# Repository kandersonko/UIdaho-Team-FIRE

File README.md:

# Team FIRE GitHub
## University of Idaho
### Collin Heist, Shelby Linafelter, and Koffi Anderson

## Existing Files

-  `/Component Test Board/`
	* This directory is for the _KiCad_ project dedicated to the __Component Test Board__.

- `/Board Redesign/`
	* This directory is for the _KiCad_ project dedicated to the __IRIDIUM 9523 carrier redesign__.
	* Within this is __Iridium Carrier (2). *__ files. These files are the Eagle project files, and the previous Senior Design Team's (Team SCUBEE) schematic and PCB files being used for reference.
	* The redesigned project is being placed within `/KiCad Project/`, and this directory contains the Eeschema and PCBnew footprints and symbols created for the purpose of this board.
	
## To Do

- Find a replacement for the LT3959 Boost circuit
- Verify the final status of `JP4` (Sim Card Enable); whether it is tied to the 5V line or the SIM enable line coming from the IRIDIUM 9523
- Verify the status of `JP1` (mode switch pin of IRIDIUM) if it's tied to GND or to the status of `JP2`.
- Verify the status of `JP2` (mode switch high-voltage jumper); if it is tied to 3.3V ISENSE line or 3.3V bus.
- Verify the status of `JP3` (RF enable reference voltage); if it is tied to 3.3V ISENSE line or 3.3V bus.
- Determine whether `S1` (the RF enable switch?) is necessary in end-product.
- Verify the status of `JP5` (the VCCA power source of `U3`); is it tied to 3.3V ISENSE or 3.3V bus.
- Determine if `JP3` (the +3.3V, +5V, and bus power voltage 3-pin header) is required in end-product.
- Decided whether the SAMD21 is adequate, or should we transition over to the SAMD51 for memory / I2C capabilities.
- Determine whether `S2` (the microcontroller reset switch) is necessary in the final product.
- Identify which test points are essential / desired.

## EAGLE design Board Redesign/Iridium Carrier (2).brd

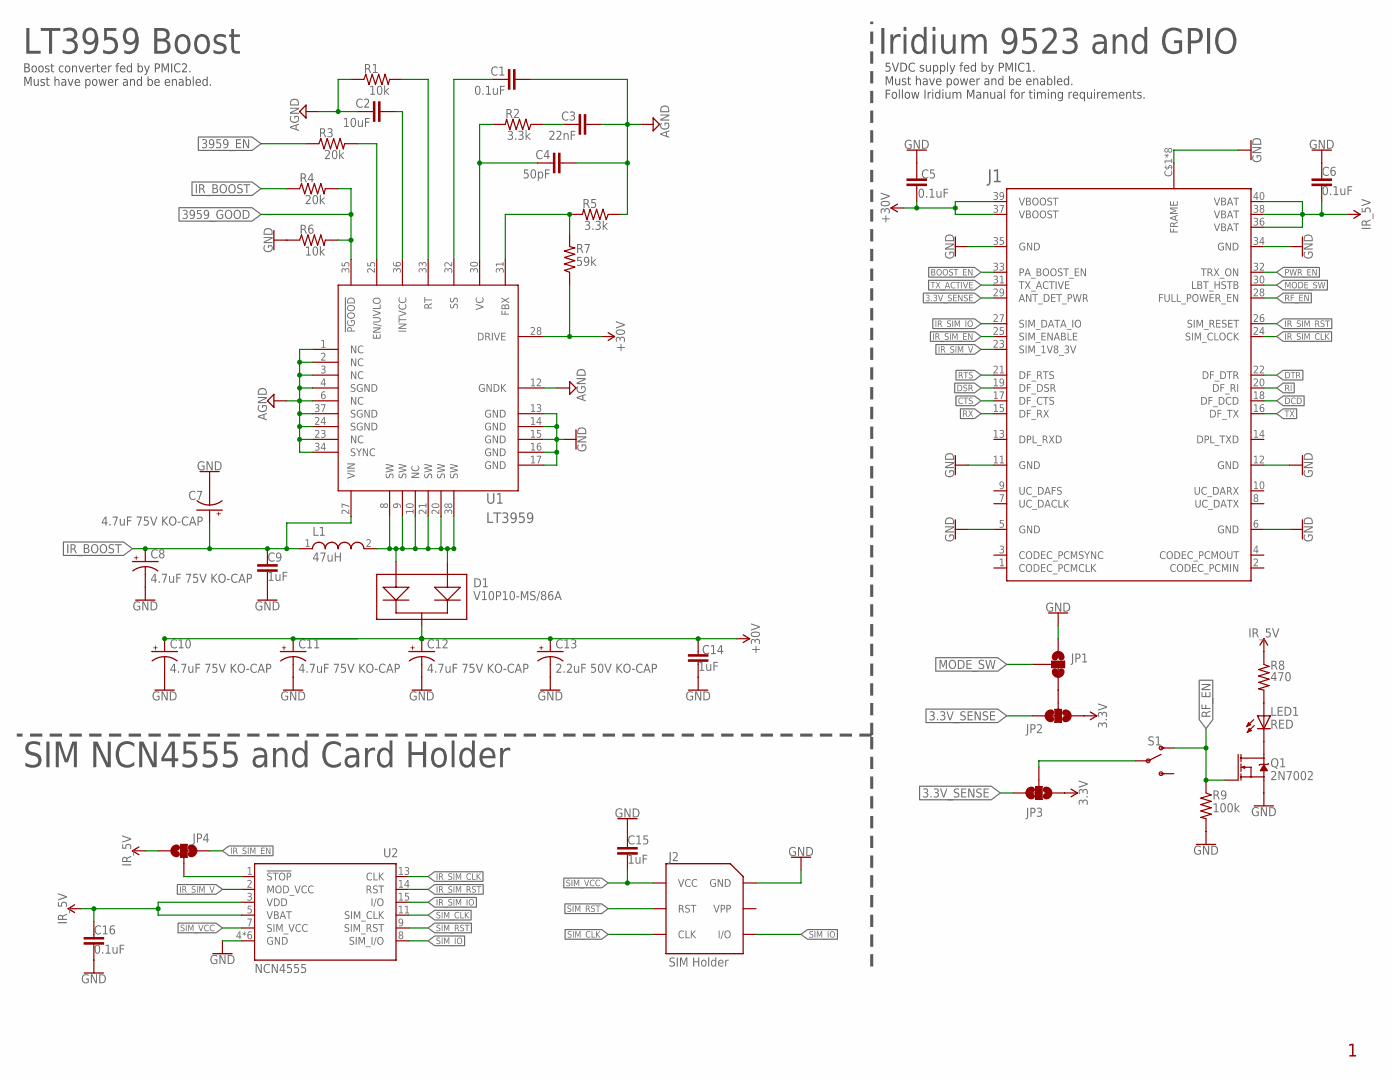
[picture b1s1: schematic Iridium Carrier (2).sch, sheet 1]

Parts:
C1, C5, C6, C16: 0.1uF; C0603
C2: 10uF; C0603
C3: 22nF; C0603
C4: 50pF; C0603
C7, C8, C10, C11, C12: 4.7uF 75V KO-CAP; D/7343-31R
C9, C14, C15: 1uF; C0603
C13: 2.2uF 50V KO-CAP; CT3528
D1: V10P10-MS/86A; DIODE_TO-277A
J1: Molex 0541020404; IRIDIUM-9523
J2: SIM Holder; SIMHOLDER
JP1: OP MODE; SMT-JUMPER_3_1-NC_TRACE_SILK
JP2, JP3: Sense V; SMT-JUMPER_3_1-NC_TRACE_SILK
JP4: SIM_STOP; SMT-JUMPER_3_1-NC_TRACE_SILK
L1: 47uH; WE-HCI_1890
LED1: RED; CHIP-LED0805
Q1: 2N7002; SOT23-3
R1, R6: 10k; R0603
R2, R5: 3.3k; R0603
R3, R4: 20k; R0603
R7: 59k; R0603
R8: 470; R0603
R9: 100k; R0603
S1: FULL RF PWR; SWITCH_SPDT_PTH_11.6X4.0MM
U1: LT3959; QFN-36_UHEMA
U2: DAVID-HANDY_ON_NCN4555DEFAULT; DAVID-HANDY_QFN16-3X3MM

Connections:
3.3V: JP2.1, JP3.1; also elsewhere on the board
3.3V_SENSE: J1.29 (ANT_DET_PWR), JP2.3, JP3.3; also elsewhere on the board
3959_EN: R3.1; also elsewhere on the board
3959_GOOD: R4.2, R6.2, U1.35 (!PGOOD!); also elsewhere on the board
AGND: C1.2, C2.1, C3.2, C4.2, R1.1, R5.1, U1.1 (NC), U1.2 (NC), U1.3 (NC), U1.4 (SGND), U1.6 (NC), U1.12 (GNDK), U1.23 (NC), U1.24 (SGND), U1.34 (SYNC), U1.37 (SGND)
BOOST_EN: J1.33 (PA_BOOST_EN); also elsewhere on the board
CTS: J1.17 (DF_CTS); also elsewhere on the board
DCD: J1.18 (DF_DCD); also elsewhere on the board
DSR: J1.19 (DF_DSR); also elsewhere on the board
DTR: J1.22 (DF_DTR); also elsewhere on the board
GND: C5.1, C6.1, C7.-, C8.-, C9.2, C10.-, C11.-, C12.-, C13.-, C14.2, C15.1, C16.1, J1.5 (GND), J1.6 (GND), J1.11 (GND), J1.12 (GND), J1.34 (GND), J1.35 (GND), J1.C$1 (FRAME), J1.C$2 (FRAME), J1.C$3 (FRAME), J1.C$4 (FRAME), J1.C$5 (FRAME), J1.C$6 (FRAME), J1.C$7 (FRAME), J1.C$8 (FRAME), J2.C5 (GND), JP1.1, Q1.2 (S), R6.1, R9.2, U1.13 (GND), U1.14 (GND), U1.15 (GND), U1.16 (GND), U1.17 (GND), U2.4 (GND), U2.6 (GND), U2.10 (GND), U2.12 (GND), U2.16 (GND), U2.EXT (GND); also elsewhere on the board
IR_BOOST: C7.+, C8.+, C9.1, L1.1, R4.1, U1.27 (VIN); also elsewhere on the board
IR_SIM_CLK: J1.24 (SIM_CLOCK), U2.13 (CLK)
IR_SIM_EN: J1.25 (SIM_ENABLE), JP4.3; also elsewhere on the board
IR_SIM_IO: J1.27 (SIM_DATA_IO), U2.15 (I/O)
IR_SIM_RST: J1.26 (SIM_RESET), U2.14 (RST)
IR_SIM_V: J1.23 (SIM_1V8_3V), U2.2 (MOD_VCC)
MODE_SW: J1.30 (LBT_HSTB), JP1.2
unnamed: JP4.2, U2.1 (!STOP)
unnamed: D1.1, D1.2, L1.2, U1.8 (SW), U1.9 (SW), U1.10 (NC), U1.20 (SW), U1.21 (SW), U1.38 (SW)
unnamed: C2.2, U1.36 (INTVCC)
unnamed: JP1.3, JP2.2
unnamed: C1.1, U1.32 (SS)
unnamed: R1.2, U1.33 (RT)
unnamed: LED1.C, Q1.3 (D)
unnamed: C4.1, R2.2, U1.30 (VC)
unnamed: C3.1, R2.1
unnamed: R5.2, R7.2, U1.31 (FBX)
unnamed: JP3.2, S1.2
unnamed: LED1.A, R8.2
unnamed: R3.2, U1.25 (EN/UVLO)
PWR_EN: J1.32 (TRX_ON); also elsewhere on the board
RF_EN: J1.28 (FULL_POWER_EN), Q1.1 (G), R9.1, S1.1 (O); also elsewhere on the board
RI: J1.20 (DF_RI); also elsewhere on the board
RTS: J1.21 (DF_RTS); also elsewhere on the board
RX: J1.15 (DF_RX); also elsewhere on the board
SIM_CLK: J2.C3 (CLK), U2.11 (SIM_CLK)
SIM_IO: J2.C7 (I/O), U2.8 (SIM_I/O)
SIM_RST: J2.C2 (RST), U2.9 (SIM_RST)
SIM_VCC: C15.2, J2.C1 (VCC), U2.7 (SIM_VCC)
TX: J1.16 (DF_TX); also elsewhere on the board
TX_ACTIVE: J1.31 (TX_ACTIVE); also elsewhere on the board
VCC: C5.2, C10.+, C11.+, C12.+, C13.+, C14.1, D1.3, J1.37 (VBOOST), J1.39 (VBOOST), R7.1, U1.28 (DRIVE); also elsewhere on the board
V_BATT: C6.2, C16.2, J1.36 (VBAT), J1.38 (VBAT), J1.40 (VBAT), JP4.1, R8.1, U2.3 (VDD), U2.5 (VBAT); also elsewhere on the board

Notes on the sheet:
Iridium 9523 and GPIO
SIM NCN4555 and Card Holder
LT3959 Boost
NCN4555
Boost converter fed by PMIC2. Must have power and be enabled.
5VDC supply fed by PMIC1. Must have power and be enabled. Follow Iridium Manual for timing requirements.

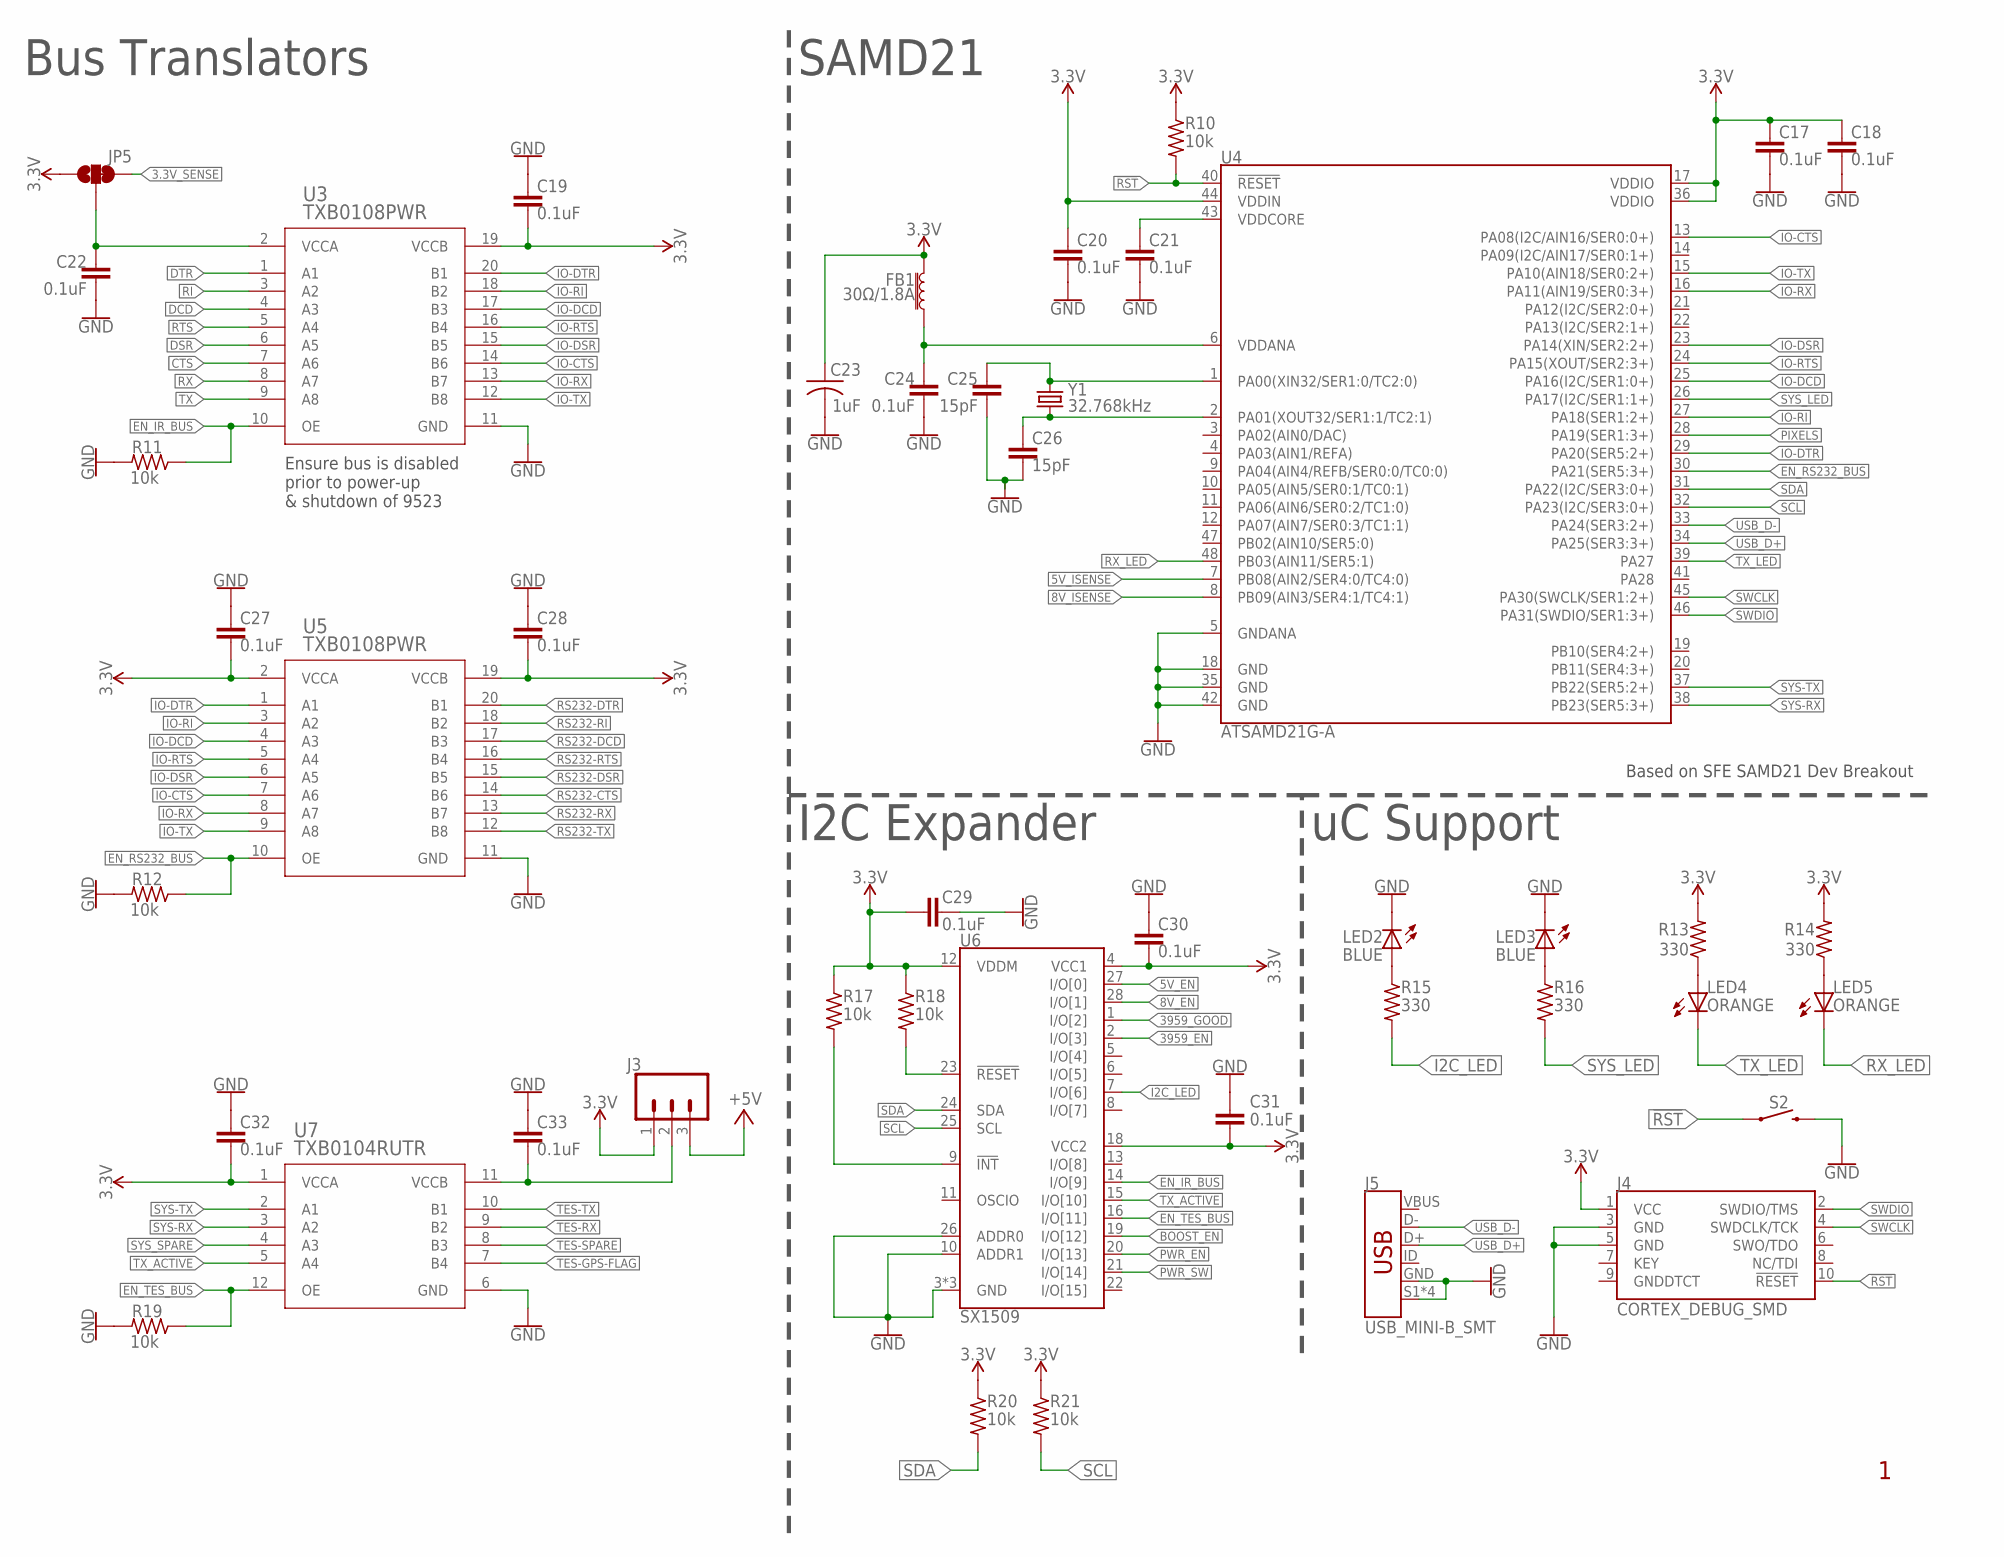
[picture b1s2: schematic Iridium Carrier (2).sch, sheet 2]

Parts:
C17, C18, C19, C20, C21, C22, C24, C27, C28, C29, C30, C31, C32, C33: 0.1uF; C0603
C23: 1uF; C0805
C25, C26: 15pF; C0603
FB1: 30Ω/1.8A; 0603
J3: 455-1750-1-ND; 1X03
J4: CORTEX_DEBUG_SMD; SAMTECH_FTSH-105-01
J5: USB_MINI-B_SMT; USB-MINIB
JP5: BUS_V; SMT-JUMPER_3_1-NC_TRACE_SILK
LED2, LED3: BLUE; CHIP-LED0805
LED4, LED5: ORANGE; CHIP-LED0805
R10, R11, R12, R17, R18, R19, R20, R21: 10k; R0603
R13, R14, R15, R16: 330; R0603
S2: RST BTN; TACTILE_SWITCH_SMD_6.0X3.5MM
U3, U5: TXB0108PWR; PW20
U4: ATSAMD21G-A; TQFP-48
U6: SX1509; QFN-28
U7: TXB0104RUTR; RUT12
Y1: 32.768kHz; CRYSTAL-SMD-3.2X1.5MM

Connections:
3.3V: C17.1, C18.1, C19.2, C20.1, C23.1, C27.2, C28.2, C29.1, C30.2, C31.2, C32.2, FB1.2, J3.1, J4.1 (VCC), JP5.1, R10.1, R13.2, R14.2, R17.1, R18.1, R20.1, R21.1, U3.19 (VCCB), U4.17 (VDDIO), U4.36 (VDDIO), U4.44 (VDDIN), U5.2 (VCCA), U5.19 (VCCB), U6.4 (VCC1), U6.12 (VDDM), U6.18 (VCC2), U7.1 (VCCA); also elsewhere on the board
3.3V_SENSE: JP5.3; also elsewhere on the board
5V_EN: U6.27 (I/O[0]); also elsewhere on the board
5V_ISENSE: U4.7 (PB08(AIN2/SER4:0/TC4:0)); also elsewhere on the board
8V_EN: U6.28 (I/O[1]); also elsewhere on the board
8V_ISENSE: U4.8 (PB09(AIN3/SER4:1/TC4:1)); also elsewhere on the board
3959_EN: U6.2 (I/O[3]); also elsewhere on the board
3959_GOOD: U6.1 (I/O[2]); also elsewhere on the board
!RST: J4.10 (!RESET), R10.2, S2.1, U4.40 (!RESET!); also elsewhere on the board
+5V: J3.3; also elsewhere on the board
BOOST_EN: U6.19 (I/O[12]); also elsewhere on the board
CTS: U3.7 (A6); also elsewhere on the board
DCD: U3.4 (A3); also elsewhere on the board
DSR: U3.6 (A5); also elsewhere on the board
DTR: U3.1 (A1); also elsewhere on the board
EN_IR_BUS: R11.1, U3.10 (OE), U6.14 (I/O[9]); also elsewhere on the board
EN_RS232_BUS: R12.1, U4.30 (PA21(SER5:3+)), U5.10 (OE); also elsewhere on the board
EN_TES_BUS: R19.1, U6.16 (I/O[11]), U7.12 (OE); also elsewhere on the board
GND: C17.2, C18.2, C19.1, C20.2, C21.2, C22.1, C23.2, C24.2, C25.2, C26.2, C27.1, C28.1, C29.2, C30.1, C31.1, C32.1, C33.1, J4.3 (GND), J4.5 (GND), J5.GND, J5.S1 (SHIELD), J5.S2 (SHIELD), J5.S3 (SHIELD), J5.S4 (SHIELD), LED2.C, LED3.C, R11.2, R12.2, R19.2, S2.2, U3.11 (GND), U4.5 (GNDANA), U4.18 (GND), U4.35 (GND), U4.42 (GND), U5.11 (GND), U6.3 (GND), U6.10 (ADDR1), U6.17 (GND), U6.26 (ADDR0), U6.29 (GND), U7.6 (GND); also elsewhere on the board
I2C_LED: R15.2, U6.7 (I/O[6])
IO-CTS: U3.14 (B6), U4.13 (PA08(I2C/AIN16/SER0:0+)), U5.7 (A6)
IO-DCD: U3.17 (B3), U4.25 (PA16(I2C/SER1:0+)), U5.4 (A3)
IO-DSR: U3.15 (B5), U4.23 (PA14(XIN/SER2:2+)), U5.6 (A5)
IO-DTR: U3.20 (B1), U4.29 (PA20(SER5:2+)), U5.1 (A1)
IO-RI: U3.18 (B2), U4.27 (PA18(SER1:2+)), U5.3 (A2)
IO-RTS: U3.16 (B4), U4.24 (PA15(XOUT/SER2:3+)), U5.5 (A4)
IO-RX: U3.13 (B7), U4.16 (PA11(AIN19/SER0:3+)), U5.8 (A7)
IO-TX: U3.12 (B8), U4.15 (PA10(AIN18/SER0:2+)), U5.9 (A8)
unnamed: C22.2, JP5.2, U3.2 (VCCA)
unnamed: C33.2, J3.2, U7.11 (VCCB)
unnamed: LED2.A, R15.1
unnamed: C24.1, FB1.1, U4.6 (VDDANA)
unnamed: C21.1, U4.43 (VDDCORE)
unnamed: C25.1, U4.1 (PA00(XIN32/SER1:0/TC2:0)), Y1.P$2 (2)
unnamed: C26.1, U4.2 (PA01(XOUT32/SER1:1/TC2:1)), Y1.P$1 (1)
unnamed: LED4.A, R13.1
unnamed: LED5.A, R14.1
unnamed: LED3.A, R16.1
unnamed: R17.2, U6.9 (!INT)
unnamed: R18.2, U6.23 (!RESET)
PIXELS: U4.28 (PA19(SER1:3+)); also elsewhere on the board
PWR_EN: U6.20 (I/O[13]); also elsewhere on the board
PWR_SW: U6.21 (I/O[14]); also elsewhere on the board
RI: U3.3 (A2); also elsewhere on the board
RS232-CTS: U5.14 (B6); also elsewhere on the board
RS232-DCD: U5.17 (B3); also elsewhere on the board
RS232-DSR: U5.15 (B5); also elsewhere on the board
RS232-DTR: U5.20 (B1); also elsewhere on the board
RS232-RI: U5.18 (B2); also elsewhere on the board
RS232-RTS: U5.16 (B4); also elsewhere on the board
RS232-RX: U5.13 (B7); also elsewhere on the board
RS232-TX: U5.12 (B8); also elsewhere on the board
RTS: U3.5 (A4); also elsewhere on the board
RX: U3.8 (A7); also elsewhere on the board
RX_LED: LED5.C, U4.48 (PB03(AIN11/SER5:1))
SCL: R21.2, U4.32 (PA23(I2C/SER3:0+)), U6.25 (SCL); also elsewhere on the board
SDA: R20.2, U4.31 (PA22(I2C/SER3:0+)), U6.24 (SDA); also elsewhere on the board
SWCLK: J4.4 (SWDCLK/TCK), U4.45 (PA30(SWCLK/SER1:2+))
SWDIO: J4.2 (SWDIO/TMS), U4.46 (PA31(SWDIO/SER1:3+))
SYS-RX: U4.38 (PB23(SER5:3+)), U7.3 (A2)
SYS-TX: U4.37 (PB22(SER5:2+)), U7.2 (A1)
SYS_LED: R16.2, U4.26 (PA17(I2C/SER1:1+))
SYS_SPARE: U7.4 (A3)
TES-GPS-FLAG: U7.7 (B4); also elsewhere on the board
TES-RX: U7.9 (B2); also elsewhere on the board
TES-SPARE: U7.8 (B3)
TES-TX: U7.10 (B1); also elsewhere on the board
TX: U3.9 (A8); also elsewhere on the board
TX_ACTIVE: U6.15 (I/O[10]), U7.5 (A4); also elsewhere on the board
TX_LED: LED4.C, U4.39 (PA27)
USB_D+: J5.D+, U4.34 (PA25(SER3:3+))
USB_D-: J5.D-, U4.33 (PA24(SER3:2+))
VBUS: J5.VBUS

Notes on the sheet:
Bus Translators
SAMD21
uC Support
I2C Expander
Based on SFE SAMD21 Dev Breakout
Ensure bus is disabled prior to power-up & shutdown of 9523

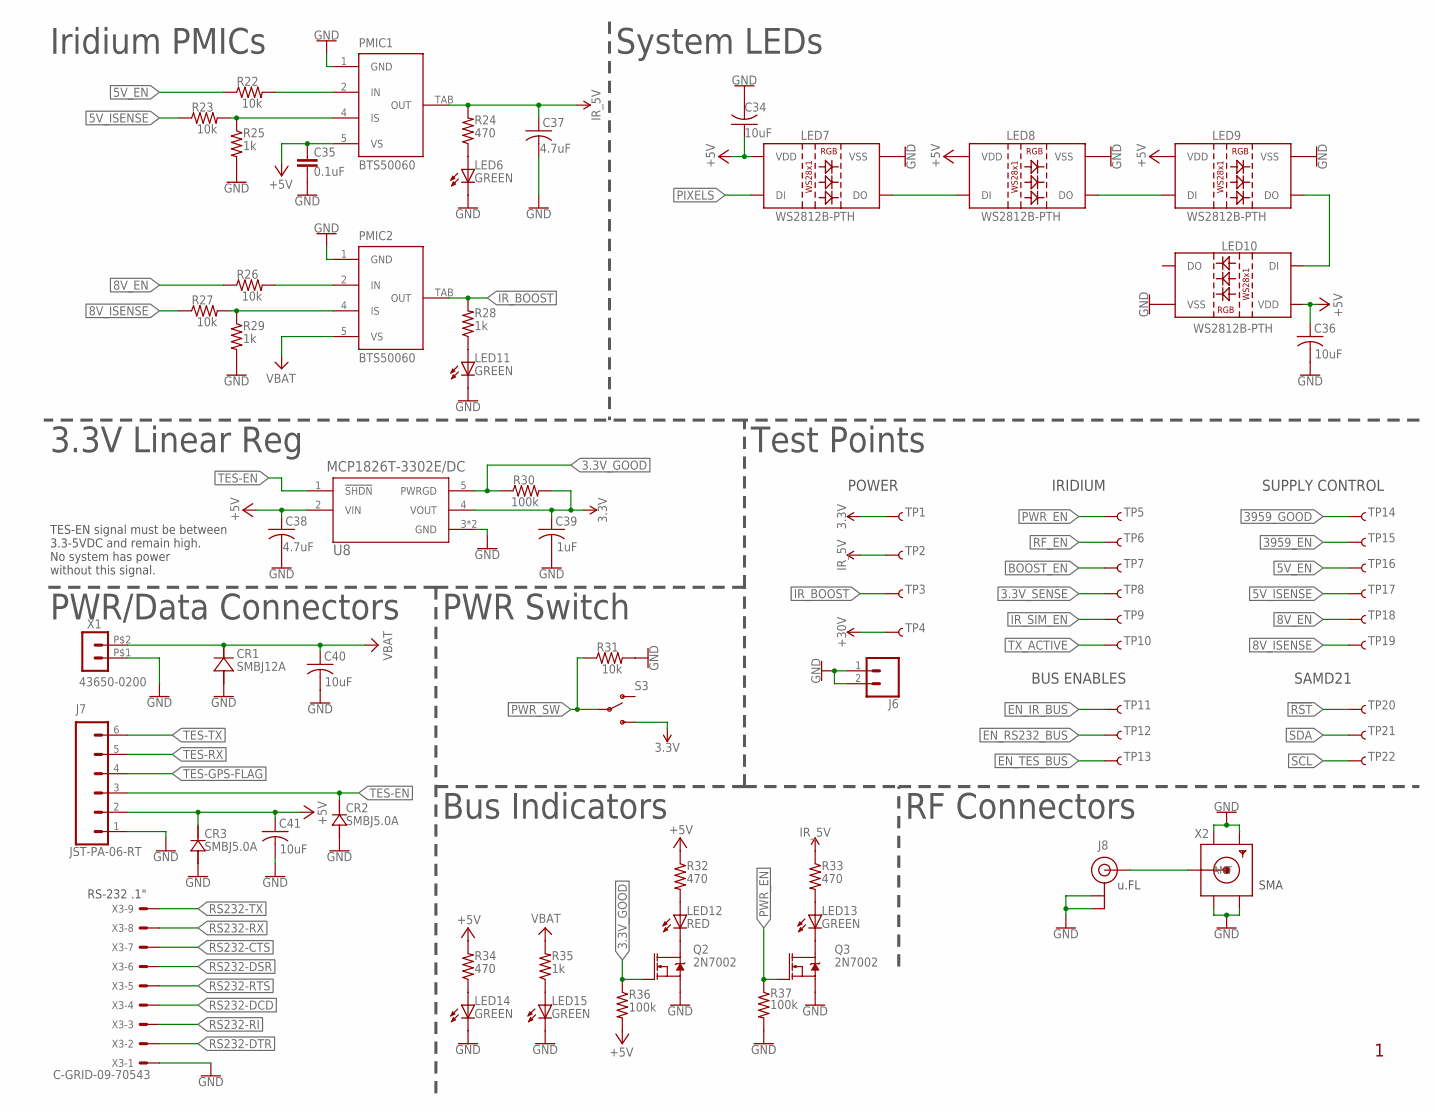
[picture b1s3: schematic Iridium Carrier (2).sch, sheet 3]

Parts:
C34, C36, C40, C41: 10uF; C1206
C35: 0.1uF; C0603
C37, C38: 4.7uF; C1206
C39: 1uF; C0805
CR1: SMBJ12A; SMB
CR2, CR3: SMBJ5.0A; DIODE_DO214AA
J6: GND; 1X02
J7: JST-PA-06-RT; 1X6-JST-PA
J8: U.FL
LED6, LED11, LED13, LED14, LED15: GREEN; CHIP-LED0805
LED7, LED8, LED9, LED10: WS2812B-PTH; WS2812B-PTH-KIT
LED12: RED; CHIP-LED0805
PMIC1, PMIC2: BTS50060; TO252-5-11
Q2, Q3: 2N7002; SOT23-3
R22, R23, R26, R27, R31: 10k; R0603
R24, R32, R33, R34: 470; R0603
R25, R28, R29, R35: 1k; R0603
R30, R36, R37: 100k; R0603
S3: PWR SW; SWITCH_SPDT_PTH_11.6X4.0MM
TP1, TP2, TP3, TP4, TP5, TP6, TP7, TP8, TP9, TP10, TP11, TP12, TP13, TP14, TP15, TP16, TP17, TP18, TP19, TP20, TP21, TP22: TEST-POINT3X4; PAD.03X.04
U8: MCP1826T-3302E/DC; SOT-223_5MC
X1: 43650-0200
X2: SMACONNECTOR; SMA90_DIP
X3: C-GRID-09-70543; 70543-09

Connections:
3.3V: C39.1, R30.2, S3.3 (S), TP1.P$1, U8.4 (VOUT); also elsewhere on the board
3.3V_GOOD: Q2.1 (G), R30.1, R36.1, U8.5 (PWRGD)
3.3V_SENSE: TP8.P$1; also elsewhere on the board
5V_EN: R22.1, TP16.P$1; also elsewhere on the board
5V_ISENSE: R23.1, TP17.P$1; also elsewhere on the board
8V_EN: R26.1, TP18.P$1; also elsewhere on the board
8V_ISENSE: R27.1, TP19.P$1; also elsewhere on the board
3959_EN: TP15.P$1; also elsewhere on the board
3959_GOOD: TP14.P$1; also elsewhere on the board
!RST: TP20.P$1; also elsewhere on the board
+5V: C34.1, C35.1, C36.1, C38.1, C41.1, CR3.1 (2), J7.2, LED7.3 (VDD), LED8.3 (VDD), LED9.3 (VDD), LED10.3 (VDD), PMIC1.5 (VS), R32.1, R34.2, R36.2, U8.2 (VIN); also elsewhere on the board
BOOST_EN: TP7.P$1; also elsewhere on the board
EN_IR_BUS: TP11.P$1; also elsewhere on the board
EN_RS232_BUS: TP12.P$1; also elsewhere on the board
EN_TES_BUS: TP13.P$1; also elsewhere on the board
GND: C34.2, C35.2, C36.2, C37.2, C38.2, C39.2, C40.2, C41.2, CR1.2 (CATHODE2), CR2.2 (1), CR3.2 (1), J6.1, J6.2, J7.1, J8.1 (GND), J8.2 (GND), LED6.C, LED7.2 (VSS), LED8.2 (VSS), LED9.2 (VSS), LED10.2 (VSS), LED11.C, LED14.C, LED15.C, PMIC1.1 (GND), PMIC2.1 (GND), Q2.2 (S), Q3.2 (S), R25.2, R29.2, R31.2, R37.2, U8.3 (GND), U8.P$1 (GND), X1.P$1 (1), X2.GND1, X2.GND2, X2.GND3, X2.GND4, X3.1; also elsewhere on the board
IR_BOOST: PMIC2.TAB (OUT), R28.2, TP3.P$1; also elsewhere on the board
IR_SIM_EN: TP9.P$1; also elsewhere on the board
unnamed: PMIC2.4 (IS), R27.2, R29.1
unnamed: PMIC2.2 (IN), R26.2
unnamed: LED7.1 (DO), LED8.4 (DI)
unnamed: LED8.1 (DO), LED9.4 (DI)
unnamed: PMIC1.4 (IS), R23.2, R25.1
unnamed: PMIC1.2 (IN), R22.2
unnamed: LED9.1 (DO), LED10.4 (DI)
unnamed: LED6.A, R24.1
unnamed: LED14.A, R34.1
unnamed: LED12.A, R32.2
unnamed: LED12.C, Q2.3 (D)
unnamed: LED15.A, R35.1
unnamed: LED11.A, R28.1
unnamed: LED13.A, R33.2
unnamed: LED13.C, Q3.3 (D)
unnamed: J8.FEED (SIGNAL), X2.ANTENNA (ANT)
PIXELS: LED7.4 (DI); also elsewhere on the board
PWR_EN: Q3.1 (G), R37.1, TP5.P$1; also elsewhere on the board
PWR_SW: R31.1, S3.2; also elsewhere on the board
RF_EN: TP6.P$1; also elsewhere on the board
RS232-CTS: X3.7; also elsewhere on the board
RS232-DCD: X3.4; also elsewhere on the board
RS232-DSR: X3.6; also elsewhere on the board
RS232-DTR: X3.2; also elsewhere on the board
RS232-RI: X3.3; also elsewhere on the board
RS232-RTS: X3.5; also elsewhere on the board
RS232-RX: X3.8; also elsewhere on the board
RS232-TX: X3.9; also elsewhere on the board
SCL: TP22.P$1; also elsewhere on the board
SDA: TP21.P$1; also elsewhere on the board
TES-EN: CR2.1 (2), J7.3, U8.1 (!SHDN)
TES-GPS-FLAG: J7.4; also elsewhere on the board
TES-RX: J7.5; also elsewhere on the board
TES-TX: J7.6; also elsewhere on the board
TX_ACTIVE: TP10.P$1; also elsewhere on the board
VBAT: C40.1, CR1.1 (ANODE1), PMIC2.5 (VS), R35.2, X1.P$2 (2)
VCC: TP4.P$1; also elsewhere on the board
V_BATT: C37.1, PMIC1.TAB (OUT), R24.2, R33.1, TP2.P$1; also elsewhere on the board

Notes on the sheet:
RS-232 .1"
Iridium PMICs
3.3V Linear Reg
PWR/Data Connectors
PWR Switch
Bus Indicators
System LEDs
RF Connectors
Test Points
POWER
IRIDIUM
BUS ENABLES
SUPPLY CONTROL
SAMD21
u.FL
SMA
TES-EN signal must be between 3.3-5VDC and remain high. No system has power without this signal.

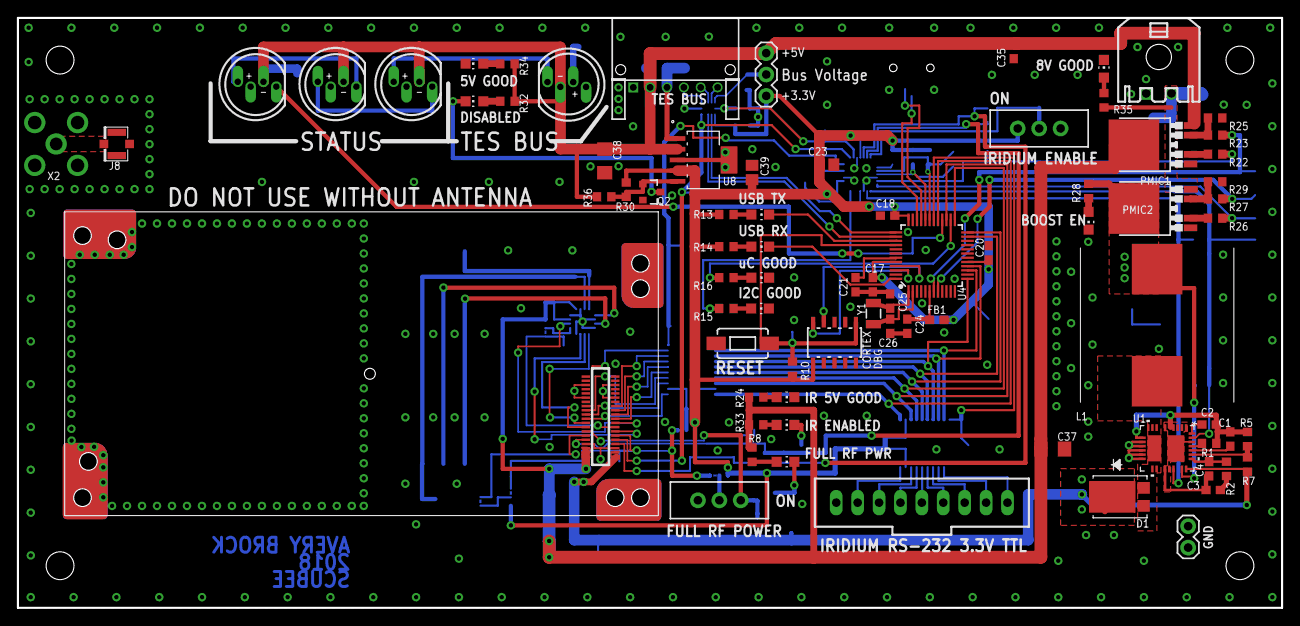
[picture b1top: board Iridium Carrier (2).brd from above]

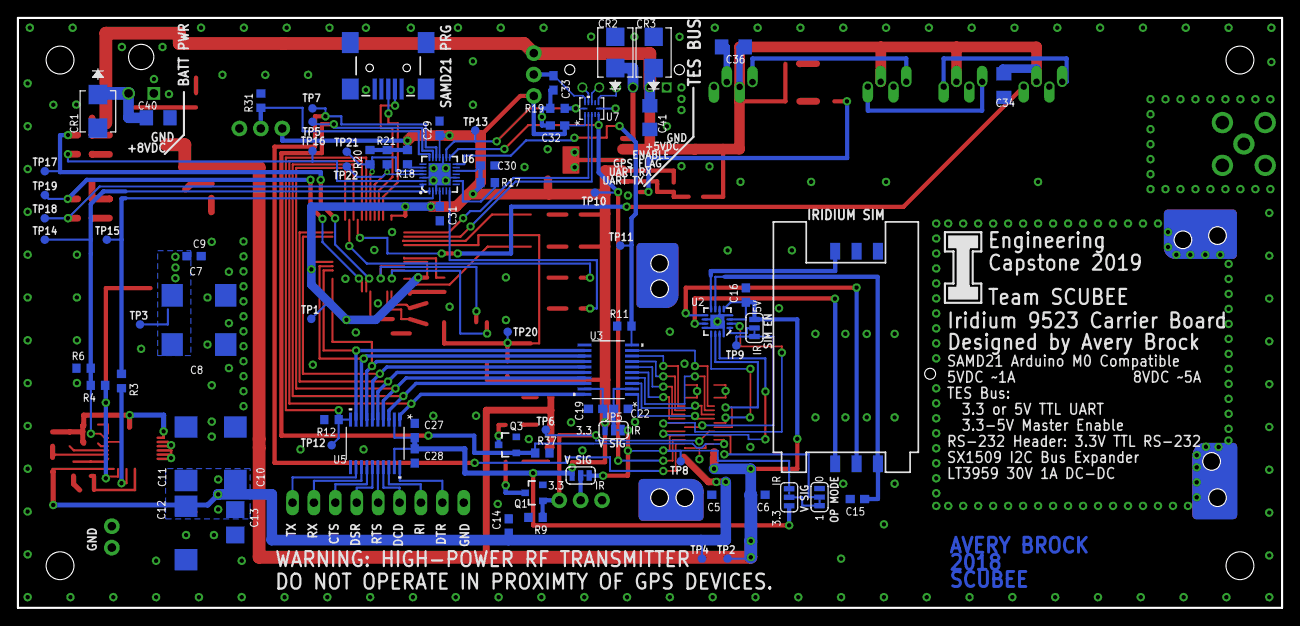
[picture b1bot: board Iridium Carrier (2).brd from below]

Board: 2 copper layers, 150.0 x 70.0 mm, 158 parts (77 on the bottom side), 117 nets.

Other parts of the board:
U$3, U$6, U$7, U$8: STAND-OFF

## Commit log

2020-01-21 Initial Component Test PCB
    - Added initial component test PCB files
    - Added starting Eagle Project and Schematic files for the IRIDIUM carrier
2020-01-23 Updated KiCad project files
2020-02-09 Started KiCad Version
2020-02-13 Removed untested components
    A bit late; removed unused components from schematic - not PCB
2020-02-14 Added 9523 User Manual
    - Added 9523 User manual
    - Started work on redesign schematic
2020-02-18 Worked more on board!
    - Moved more of the schematic over to KiCad
    - Created models and footprints / symbols for a few components
2020-02-19 Hecho más progreso
    - Added I2C bus converter
    - Added all voltage translators
    - Created hierarchical schematics
2020-02-20 Added I2C Expander
    - Added all required connections for the I2C expander
2020-02-21 Made more progress on board redesign
    - Primarily deleted useless (for our purposes) items from the old schematic so we do not have to spend time transferring them over.
    - Finished some component transfer
    - Renamed some folders
2020-02-21 Added to-do list to README
2020-02-25 Team-FIRE-v2.zip
    Archived project file (sending to new branch w/ pull request because I don't know how to use GitHub properly with these types of files :D)
2020-02-27 Fix: added files to ignore
2020-02-28 Added Shelby's work
2020-02-28 Added changes to SCH1
    - Added Shelby's changes to SCH1
2020-03-05 Deleted problematic file
    Hope this helps, Shelby!
2020-03-05 Try this!
2020-03-05 ...now?
2020-03-05 Now!
2020-03-05 Added SAMD51
    - Created schematic symbol, footprint, and 3D model for the SAMD51
    - Added SAMD51 to the schematic (only partially implemented)
    - Added decoupling capacitors to the 3.3V bus (as recommended by the SAMD51 design manual)
    - Started checklist for SAMD51 implementation on the top-level schematic sheet; there's no convenient breakout board to emulate
    - Implemented power connections for SAMD51
2020-03-10 Added SAMD51 Breakout
2020-03-11 Fix: modified gitignore to fix some files that were tracked
2020-03-11 Add: reset button and some comments
2020-03-11 Add: swclk pin connection for reliability of operation of the SAMD51
2020-03-12 Smol changes
2020-03-12 Add: crystall oscillator and made some updates
2020-03-12 Add: no connection flag for (NC) no connect
2020-03-12 Fix: updated some comments
2020-03-12 Deleted Old Boost...
2020-03-12 Fix: moved some parts
2020-03-12 Fix: added missing wiring to crystal oscillator
2020-04-23 Updated .gitignore
2020-04-23 Finished RF Connector
    - Fixed alignment of schematic sheet 2
    - Crated U.F connector symbol, layout, and 3D symbol
    - Created coax symbol, layout, and 3D symbol
    - Added RF connector to Schematic sheet 3
2020-04-23 Minor label fix on RF connector
    - Removed display of "value" field on RF connector, changed display to MPN on both
2020-04-23 Boost Added
2020-04-24 Added PMIC part, 3.3V lin reg part, and buck converter + testpoint part
2020-04-24 Added BOM
    - Removed .csv from .gitignore
    - Added BOM output
    - Removed graphic from PCB
2020-04-24 Added TES connector
    - Added the two 1x3 connectors to page 3 of the schematic
2020-04-24 Finished RF Connector
    - Deleted old 132136RP antenna connector
    - Added new MMCX antenna connector footprint, symbol, and 3D model
    - Added MMCX antenna and U.FL connector to Schematic Page 3
2020-04-27 Fix: refactor symbol and modified schematics
2020-04-27 Finished PMICs
    - Finished stuff on schematic page 3!
2020-04-27 Progress
    - Corrected many footprint errors on components
    - Finalized work on schematic 3
2020-04-27 Buck Converter & Test Points
2020-04-28 Fix connections
2020-04-28 Update SAMD51

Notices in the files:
parts and their libraries:
SparkFun-Switches: Licensing: Creative Commons ShareAlike 4.0 International - https://creativecommons.org/licenses/by-sa/4.0
Wurth_Elektronik_Passive_rev16c: Copyright: Würth Elektronik
